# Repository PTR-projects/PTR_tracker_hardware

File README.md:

# PTR-Tracker hardware repository
Here you'll find the design files for the Tracker PCB

Looking for software? That's [here](https://github.com/PTR-projects/PTR_tracker_firmware)

# How to order
The folders contain the kicad projects and JLC assembly files for the 2 frequency variants of the device.

You can order the PCBs and solder them yourself, or use JLC's assembly service. Pick the frequency variant, and open the `PRODUCTION` folder. There you'll find the gerbers, BOM, and footprint positions. The only parameter you need to tick is to specify the order number location, we hid it under the GPS antenna. Don't forget to pick a color!

# Required parts
Only 1 side of the board will be soldered by JLC. You need to install an SMD dip switch, 2 0603 LEDs, a GPS antenna and an SMA connector.

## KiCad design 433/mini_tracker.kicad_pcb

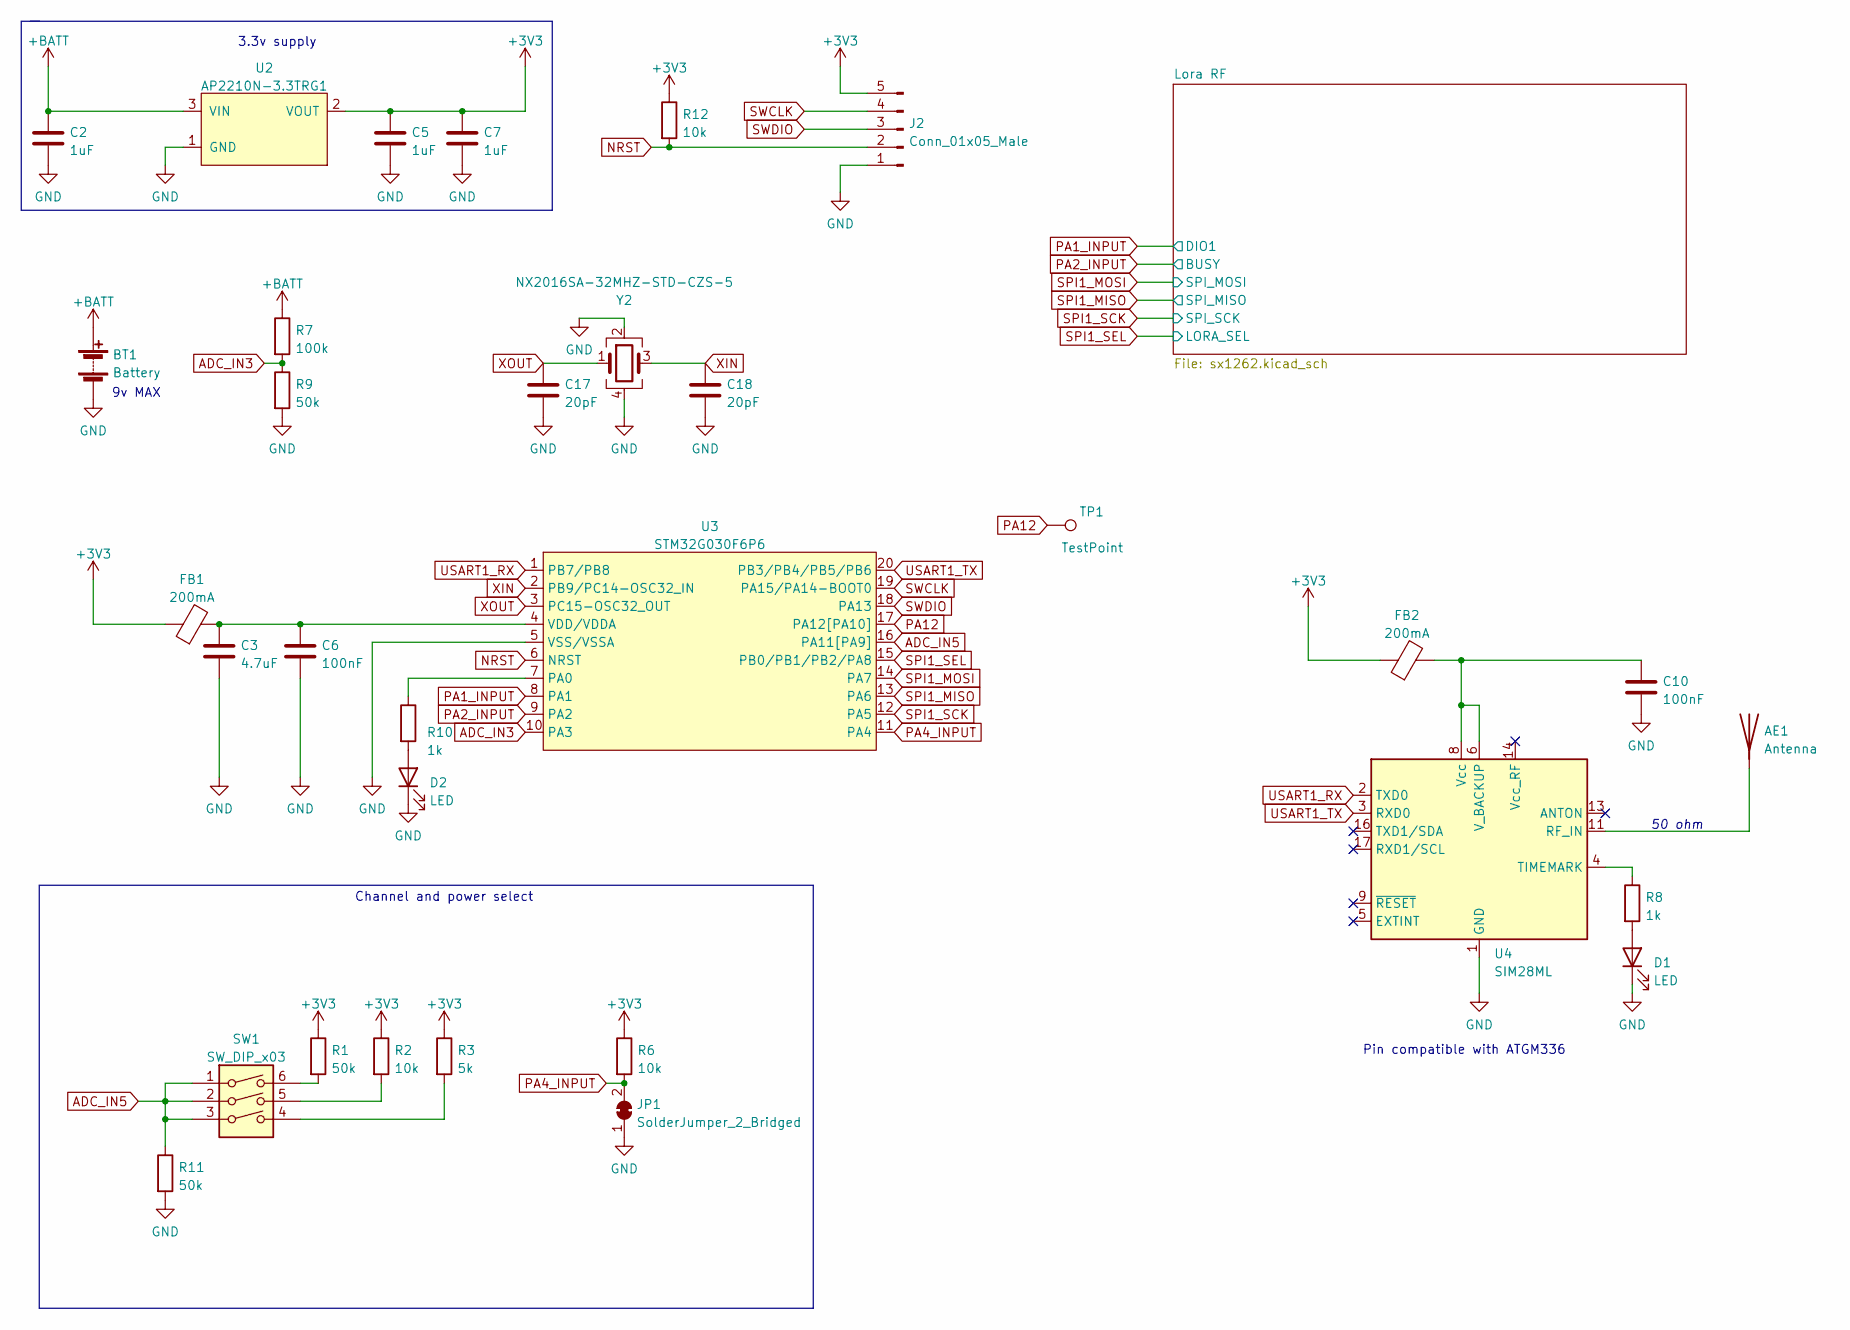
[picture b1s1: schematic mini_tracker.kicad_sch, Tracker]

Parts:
AE1: Antenna; ANT1575-1540D
BT1: Battery; sturdy_2.54_battery_screw
C2, C5, C7: 1uF; C_0402_1005Metric; LCSC C52923
C3: 4.7uF; C_0402_1005Metric; LCSC C23733
C6, C10: 100nF; C_0402_1005Metric; LCSC C1525
C17, C18: 20pF; C_0402_1005Metric; LCSC C1554
D1, D2: LED; LED_0603_1608Metric
FB1, FB2: 200mA; L_0603_1608Metric; LCSC C1002
J2: Conn_01x05_Male; PinHeader_1x05_P2.54mm_Vertical
JP1: SolderJumper_2_Bridged; SolderJumper-2_P1.3mm_Bridged_RoundedPad1.0x1.5mm
R1, R9, R11: 50k; R_0402_1005Metric; LCSC C25794
R2, R6, R12: 10k; R_0402_1005Metric; LCSC C25744
R3: 5k; R_0402_1005Metric; LCSC C25905
R7: 100k; R_0402_1005Metric; LCSC C25741
R8, R10: 1k; R_0402_1005Metric; LCSC C11702
SW1: SW_DIP_x03; ESD103EZ
TP1: TestPoint; TestPoint_Pad_D1.5mm
U2: AP2210N-3.3TRG1; SOT-23; LCSC C155508
U3: STM32G030F6P6; TSSOP-20_4.4x6.5mm_P0.65mm; LCSC C529330
U4: SIM28ML; LCSC C90770
Y2: NX2016SA-32MHZ-STD-CZS-5; Crystal_SMD_2016-4Pin_2.0x1.6mm; LCSC C843260

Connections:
+3V3: C5.1, C7.1, FB1.1, FB2.1, J2.5, R1.1, R2.1, R3.1, R6.1, R12.1, U2.2 (VOUT); also elsewhere on the board
+BATT: BT1.1 (+), C2.1, R7.1, U2.3 (VIN)
ADC_IN3: R7.2, R9.1, U3.10 (PA3)
ADC_IN5: R11.1, SW1.1, SW1.2, SW1.3, U3.16 (PA11[PA9])
GND: BT1.2 (-), C2.2, C3.2, C5.2, C6.2, C7.2, C10.2, C17.2, C18.2, D1.1 (K), D2.1 (K), J2.1, JP1.1 (A), R9.2, R11.2, U2.1 (GND), U3.5 (VSS/VSSA), U4.1 (GND), U4.10 (GND), U4.12 (GND), Y2.2, Y2.4; also elsewhere on the board
NRST: J2.2, R12.2, U3.6 (NRST)
unnamed: AE1.1 (A), U4.11 (RF_IN)
unnamed: D1.2 (A), R8.2
unnamed: D2.2 (A), R10.2
unnamed: R1.2, SW1.6
unnamed: R2.2, SW1.5
unnamed: R3.2, SW1.4
unnamed: R10.1, U3.7 (PA0)
unnamed: C3.1, C6.1, FB1.2, U3.4 (VDD/VDDA)
unnamed: R8.1, U4.4 (TIMEMARK)
unnamed: C10.1, FB2.2, U4.6 (V_BACKUP), U4.8 (Vcc)
PA1_INPUT: U3.8 (PA1); also elsewhere on the board
PA2_INPUT: U3.9 (PA2); also elsewhere on the board
PA4_INPUT: JP1.2 (B), R6.2, U3.11 (PA4)
PA12: TP1.1, U3.17 (PA12[PA10])
SPI1_MISO: U3.13 (PA6); also elsewhere on the board
SPI1_MOSI: U3.14 (PA7); also elsewhere on the board
SPI1_SCK: U3.12 (PA5); also elsewhere on the board
SPI1_SEL: U3.15 (PB0/PB1/PB2/PA8); also elsewhere on the board
SWCLK: J2.4, U3.19 (PA15/PA14-BOOT0)
SWDIO: J2.3, U3.18 (PA13)
USART1_RX: U3.1 (PB7/PB8), U4.2 (TXD0)
USART1_TX: U3.20 (PB3/PB4/PB5/PB6), U4.3 (RXD0)
XIN: C18.1, U3.2 (PB9/PC14-OSC32_IN), Y2.3
XOUT: C17.1, U3.3 (PC15-OSC32_OUT), Y2.1

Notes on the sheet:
3.3v supply
Channel and power select
9v MAX
50 ohm
Pin compatible with ATGM336

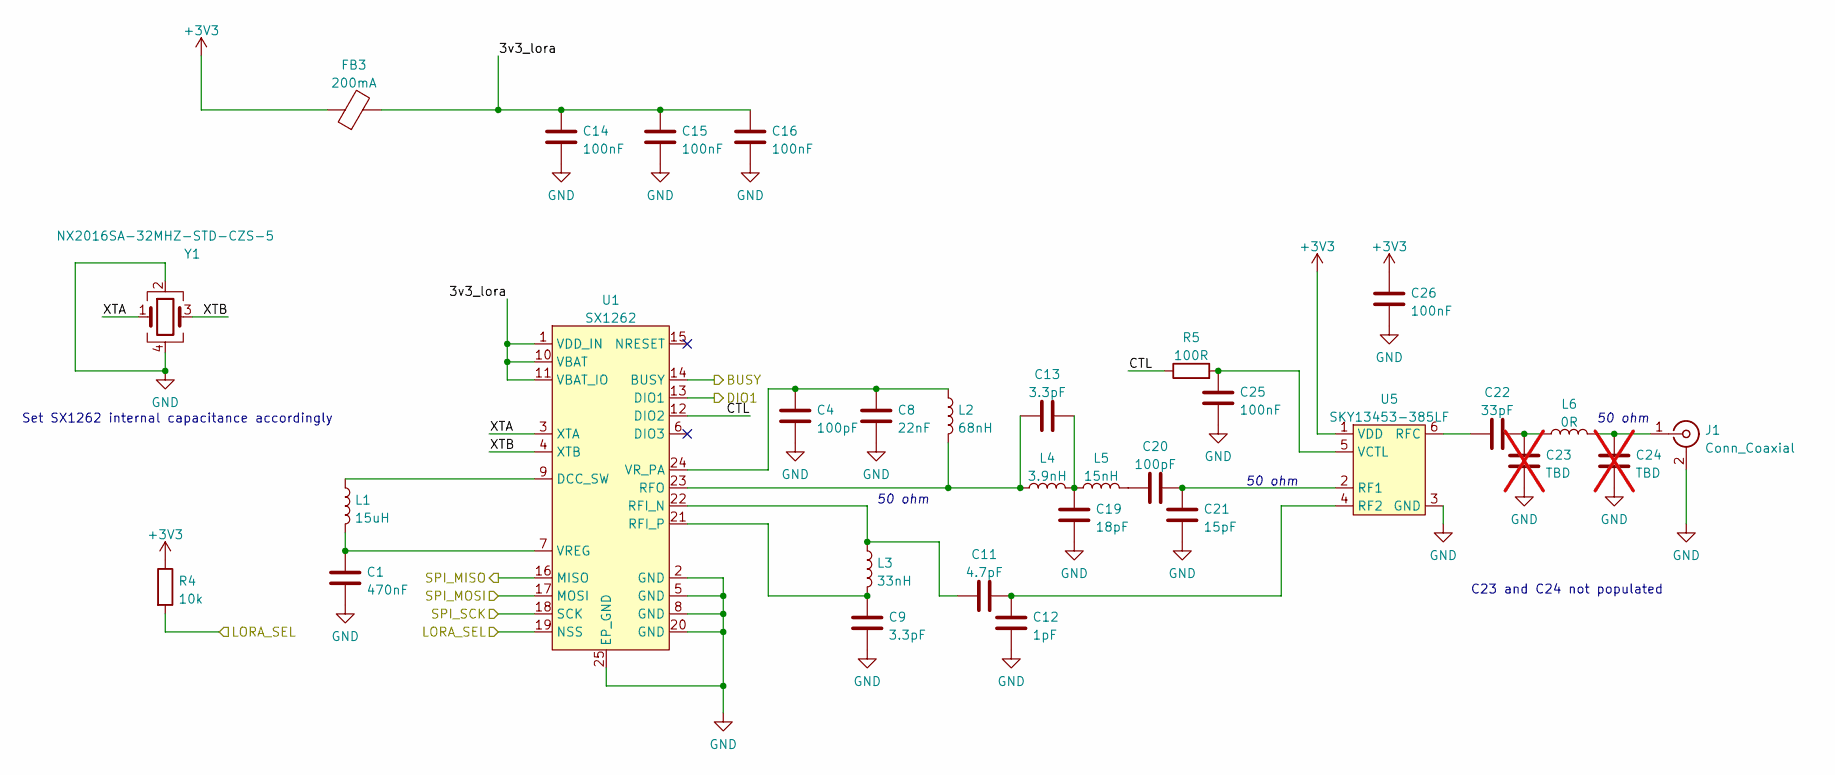
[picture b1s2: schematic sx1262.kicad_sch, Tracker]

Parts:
C1: 470nF; C_0402_1005Metric; LCSC C47339
C4, C20: 100pF; C_0402_1005Metric; LCSC C1546
C8: 22nF; C_0402_1005Metric; LCSC C1532
C9, C13: 3.3pF; C_0402_1005Metric; LCSC C1565
C11: 4.7pF; C_0402_1005Metric; LCSC C1569
C12: 1pF; C_0402_1005Metric; LCSC C1550
C14, C15, C16, C25, C26: 100nF; C_0402_1005Metric; LCSC C1525
C19: 18pF; C_0402_1005Metric; LCSC C1549
C21: 15pF; C_0402_1005Metric; LCSC C1548
C22: 33pF; C_0402_1005Metric; LCSC C1562
C23, C24: TBD; C_0402_1005Metric; not fitted
FB3: 200mA; L_0603_1608Metric; LCSC C1002
J1: Conn_Coaxial; SMA_Samtec_SMA-J-P-X-ST-EM1_EdgeMount
L1: 15uH; L_0603_1608Metric; LCSC C431252
L2: 68nH; L_0402_1005Metric; LCSC C391307
L3: 33nH; L_0402_1005Metric; LCSC C275323
L4: 3.9nH; L_0402_1005Metric; LCSC C14033
L5: 15nH; L_0402_1005Metric; LCSC C27143
L6: 0R; L_0402_1005Metric; LCSC C17168
R4: 10k; R_0402_1005Metric; LCSC C25744
R5: 100R; R_0402_1005Metric; LCSC C25076
U1: SX1262; QFN-24-1EP_4x4mm_P0.5mm_EP2.7x2.7mm; LCSC C191341
U5: SKY13453-385LF; QFN_6_1x1mm; LCSC C150878
Y1: NX2016SA-32MHZ-STD-CZS-5; Crystal_SMD_2016-4Pin_2.0x1.6mm; LCSC C843260

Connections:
+3V3: C26.2, FB3.1, R4.1, U5.1 (VDD); also elsewhere on the board
/Lora RF/3v3_lora: C14.1, C15.1, C16.1, FB3.2, U1.1 (VDD_IN), U1.10 (VBAT), U1.11 (VBAT_IO)
/Lora RF/CTL: R5.1, U1.12 (DIO2)
/Lora RF/XTA: U1.3 (XTA), Y1.1
/Lora RF/XTB: U1.4 (XTB), Y1.3
GND: C1.2, C4.2, C8.2, C9.1, C12.1, C14.2, C15.2, C16.2, C19.1, C21.1, C23.1, C24.1, C25.1, C26.1, J1.2 (Ext), U1.2 (GND), U1.5 (GND), U1.8 (GND), U1.20 (GND), U1.25 (EP_GND), U5.3 (GND), Y1.2, Y1.4; also elsewhere on the board
unnamed: C13.2, C19.2, L4.2, L5.1
unnamed: C20.1, L5.2
unnamed: C22.2, C23.2, L6.1
unnamed: C24.2, J1.1 (In), L6.2
unnamed: L1.1, U1.9 (DCC_SW)
unnamed: C11.1, L3.1, U1.22 (RFI_N)
unnamed: C9.2, L3.2, U1.21 (RFI_P)
unnamed: C13.1, L2.2, L4.1, U1.23 (RFO)
unnamed: C1.1, L1.2, U1.7 (VREG)
unnamed: C4.1, C8.1, L2.1, U1.24 (VR_PA)
unnamed: C20.2, C21.2, U5.2 (RF1)
unnamed: C11.2, C12.2, U5.4 (RF2)
unnamed: C22.1, U5.6 (RFC)
unnamed: C25.2, R5.2, U5.5 (VCTL)
PA1_INPUT: U1.13 (DIO1); also elsewhere on the board
PA2_INPUT: U1.14 (BUSY); also elsewhere on the board
SPI1_MISO: U1.16 (MISO); also elsewhere on the board
SPI1_MOSI: U1.17 (MOSI); also elsewhere on the board
SPI1_SCK: U1.18 (SCK); also elsewhere on the board
SPI1_SEL: R4.2, U1.19 (NSS); also elsewhere on the board

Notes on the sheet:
Set SX1262 internal capacitance accordingly
50 ohm
C23 and C24 not populated

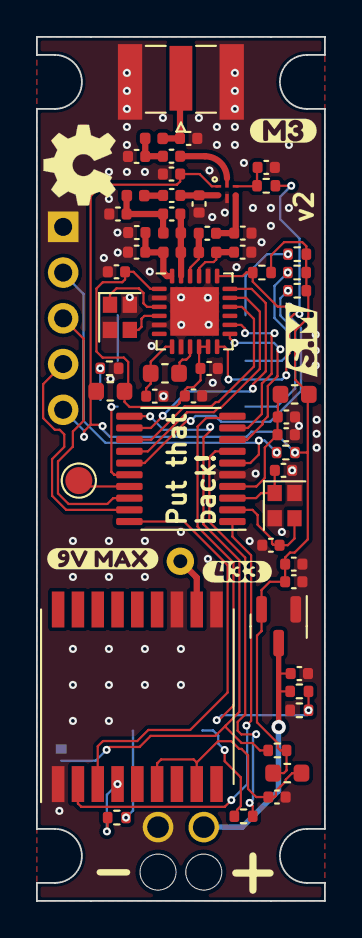
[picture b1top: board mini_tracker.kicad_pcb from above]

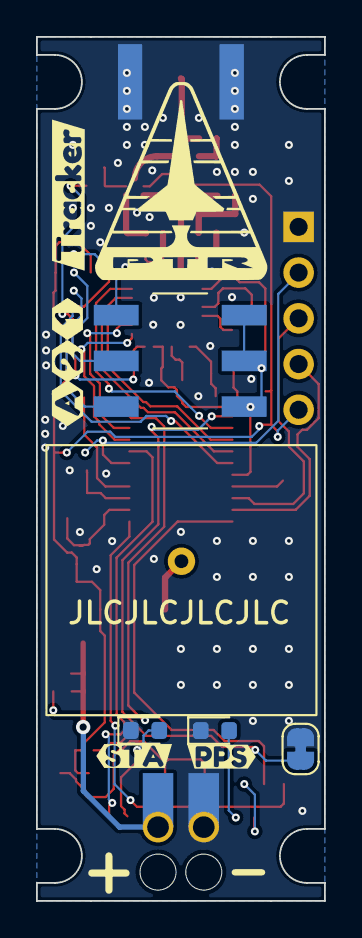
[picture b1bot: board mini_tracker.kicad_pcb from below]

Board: 2 copper layers, 16.0 x 48.0 mm, 73 parts (13 on the bottom side), 48 nets.

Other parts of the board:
kibuzzard-63C2A8A3: G***; kibuzzard-63C2A8A3
kibuzzard-63C2A895: G***; kibuzzard-63C2A895
kibuzzard-65A3B6E4: G***; kibuzzard-65A3B6E4
kibuzzard-65ED941B: G***; kibuzzard-65ED941B
kibuzzard-65ED9408: G***; kibuzzard-65ED9408
kibuzzard-640F0FCE: G***; kibuzzard-640F0FCE
kibuzzard-640F1272: G***; kibuzzard-640F1272
kibuzzard-6408E8C9: G***; kibuzzard-6408E8C9
kibuzzard-65194BBF: G***; kibuzzard-65194BBF
kibuzzard-64020663: G***; kibuzzard-64020663

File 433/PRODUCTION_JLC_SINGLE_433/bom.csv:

Designator,Footprint,Quantity,Value,LCSC Part #
AE1,ANT1575-1540D,1,Antenna,
BT1,sturdy_2.54_battery_screw,1,Battery,
C1,0402,1,470nF,C47339
"C10, C14, C15, C16, C25, C26, C6",0402,7,100nF,C1525
C11,0402,1,4.7pF,C1569
C12,0402,1,1pF,C1550
"C13, C9",0402,2,3.3pF,C1565
"C17, C18",0402,2,20pF,C1554
C19,0402,1,18pF,C1549
"C2, C5, C7",0402,3,1uF,C52923
"C20, C4",0402,2,100pF,C1546
C21,0402,1,15pF,C1548
C22,0402,1,33pF,C1562
"C23, C24",0402,2,TBD,
C3,0402,1,4.7uF,C23733
C8,0402,1,22nF,C1532
"D1, D2",0603,2,LED,
"FB1, FB2, FB3",0603,3,200mA,C1002
J1,SMA_Samtec_SMA-J-P-X-ST-EM1_EdgeMount,1,Conn_Coaxial,
J2,PinHeader_1x05_P2.54mm_Vertical,1,Conn_01x05_Male,
JP1,SolderJumper-2_P1.3mm_Bridged_RoundedPad1.0x1.5mm,1,SolderJumper_2_Bridged,
L1,0603,1,15uH,C431252
L2,0402,1,68nH,C391307
L3,0402,1,33nH,C275323
L4,0402,1,3.9nH,C14033
L5,0402,1,15nH,C27143
L6,0402,1,0R,C17168
"R1, R11, R9",0402,3,50k,C25794
"R10, R8",0402,2,1k,C11702
"R12, R2, R4, R6",0402,4,10k,C25744
R3,0402,1,5k,C25905
R5,0402,1,100R,C25076
R7,0402,1,100k,C25741
SW1,ESD103EZ,1,SW_DIP_x03,
TP1,TestPoint_Pad_D1.5mm,1,TestPoint,
U1,QFN-24-1EP_4x4mm_P0.5mm_EP2.7x2.7mm,1,SX1262,C191341
U2,SOT-23,1,AP2210N-3.3TRG1,C155508
U3,TSSOP-20_4.4x6.5mm_P0.65mm,1,STM32G030F6P6,C529330
U4,SIM28ML,1,SIM28ML,C90770
U5,QFN_6_1x1mm,1,SKY13453-385LF,C150878
"Y1, Y2",Crystal_SMD_2016-4Pin_2.0x1.6mm,2,NX2016SA-32MHZ-STD-CZS-5,C843260

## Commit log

2024-01-14 Tracker V2 433
    V2 of the tracker, 433MHz version
2024-01-14 Tracker V2 868
    V2 of the tracker, 868/915MHz broadband version
2024-01-14 cleanup and rename old files
2024-01-14 add .step
    this is probably broken
2024-01-14 Update gitignore
    now include SMT assembly files
2024-01-14 SMT assembly files
2024-01-16 Update readme
    fix broken link to firmware repo
2025-01-17 Update production files
    -Fixed sta and pps label swap for both versions
    -Completely redesign passive network for 868 version for lower extended components fee
2025-01-17 Physical drawing
